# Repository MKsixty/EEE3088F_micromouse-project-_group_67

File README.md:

# EEE3088F_micromouse-project-_group_67

Overview

This repository contains the design files, documentation, and testing results for the sensor subsystem of a Micromouse robot, developed as part of the EEE3088F course at the University of Cape Town. The sensor board is designed as a custom PCB inspired by the UCLA Micromouse project but tailored through specific design decisions to meet project requirements and ensure optimal performance. Its primary role is to provide reliable wall detection on the front, left, and right sides of the Micromouse to enable autonomous maze navigation.

Design Summary

Emitters & Detectors: Uses IR333C infrared LEDs and TEFT4300 phototransistors, chosen for their closely matched wavelength (≈940 nm) for fast response and accurate detection.

Emitter Circuit: Powered by the 3.7 V LiPo battery, with 47 Ω current-limiting resistors ensuring ~70 mA drive for strong radiant intensity. 4.7 μF bypass capacitors filter noise on the LED supply.

Switching: Implemented with MMBF170 N-channel MOSFETs driven by STM32L476 PWM GPIOs. Gate resistors (100 Ω) and pulldowns (47 kΩ) ensure safe and stable operation.

Receiver Circuit: Uses a voltage divider (470 Ω & 1.5 kΩ) to keep outputs <3.3 V for STM32 ADC compatibility. A unity-gain buffer with LM324 op-amp protects ADC inputs from noise and spikes.

Form Factor: PCB dimensions ≤70 mm × 30 mm, cost-effective, and compatible with standard JLCPCB manufacturing limits.

Failure Management: Includes test points, through-hole components for easy rework, and jumper options to adjust resistor networks if needed.

Features

Accurate wall detection at up to 15 cm.

PWM-controlled IR switching for power efficiency.

Designed for direct integration with the STM32L476 processor board via a 14×2 pin header.

Supports three independent sensor channels (front, left, right).

Repository Contents

PCB design files and schematics.

Component datasheets (IR333C, TEFT4300, LM324, MOSFETs).

Integration code for STM32L476 (sensor readout and PWM control).

Project report, test logs, and acceptance test procedures.

Testing

The board underwent short-circuit checks, current consumption tests, PWM switching validation, and functional wall-detection tests. Issues such as LED orientation errors and interference between sensors were identified and mitigated using jumper reconfiguration and potential PWM timing adjustments in firmware.

Future Improvements

Implement time-multiplexed PWM driving to reduce crosstalk between sensors.

Optimize current draw to meet <100 mA power efficiency target.

Explore improved ADC filtering for cleaner sensor output.

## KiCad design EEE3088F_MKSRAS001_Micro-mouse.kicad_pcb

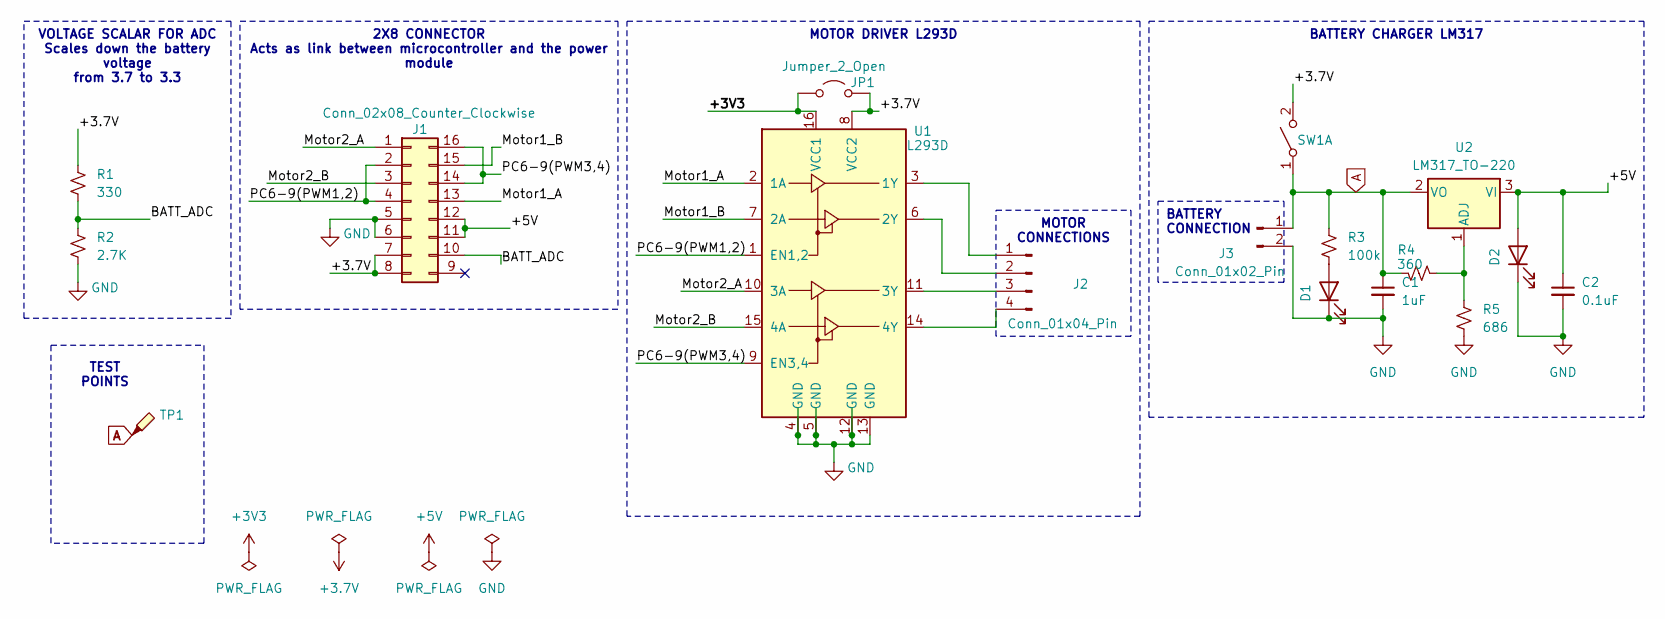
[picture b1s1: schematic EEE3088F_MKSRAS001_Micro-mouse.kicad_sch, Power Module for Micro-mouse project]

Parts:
C1: 1uF; C_0201_0603Metric
C2: 0.1uF; C_0201_0603Metric
D1, D2: LED; LED_0201_0603Metric
J1: Conn_02x08_Counter_Clockwise; JST_PUD_B16B-PUDSS_2x08_P2.00mm_Vertical
J2: Conn_01x04_Pin; PinHeader_1x04_P1.00mm_Vertical
J3: Conn_01x02_Pin; JST_PH_B2B-PH-K_1x02_P2.00mm_Vertical
JP1: Jumper_2_Open; KEYSTONE_5110
R1: 330; R_0201_0603Metric
R2: 2.7K; R_0201_0603Metric
R3: 100k; R_0201_0603Metric
R4: 360; R_0201_0603Metric
R5: 686; R_0201_0603Metric
SW1: SW_DPST_x2; SW_DIP_SPSTx01_Slide_Omron_A6S-110x_W8.9mm_P2.54mm
TP1: TestPoint_Probe; Pin_D1.0mm_L10.0mm
U1: L293D; DIP-16_W7.62mm
U2: LM317_TO-220; TO-220-3_Vertical

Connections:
+3.7V: J1.7, J1.8, JP1.2 (B), R1.1, SW1.2 (B), U1.8 (VCC2)
+3V3: JP1.1 (A), U1.16 (VCC1)
+5V: C2.1, D2.2 (A), J1.11, J1.12, U2.3 (VI)
/BATT_ADC: J1.10, R1.2, R2.1
/Motor1_A: J1.13, U1.2 (1A)
/Motor1_B: J1.15, U1.7 (2A)
/Motor2_A: J1.1, U1.10 (3A)
/Motor2_B: J1.3, U1.15 (4A)
/PC6-9(PWM1,2): J1.2, J1.4, U1.1 (EN1,2)
/PC6-9(PWM3,4): J1.14, J1.16, U1.9 (EN3,4)
A: C1.1, J3.1, R3.1, R4.2, SW1.1 (A), TP1.1, U2.2 (VO)
GND: C1.2, C2.2, D1.1 (K), D2.1 (K), J1.5, J1.6, J3.2, R2.2, R5.2, U1.4 (GND), U1.5 (GND), U1.12 (GND), U1.13 (GND)
unnamed: D1.2 (A), R3.2
unnamed: J2.1, U1.3 (1Y)
unnamed: J2.2, U1.6 (2Y)
unnamed: J2.3, U1.11 (3Y)
unnamed: J2.4, U1.14 (4Y)
unnamed: R4.1, R5.1, U2.1 (ADJ)

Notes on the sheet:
2X8 CONNECTOR Acts as link between microcontroller and the power module
BATTERY CHARGER LM317
MOTOR DRIVER L293D
BATTERY CONNECTION
TEST POINTS
MOTOR CONNECTIONS
VOLTAGE SCALAR FOR ADC Scales down the battery voltage from 3.7 to 3.3

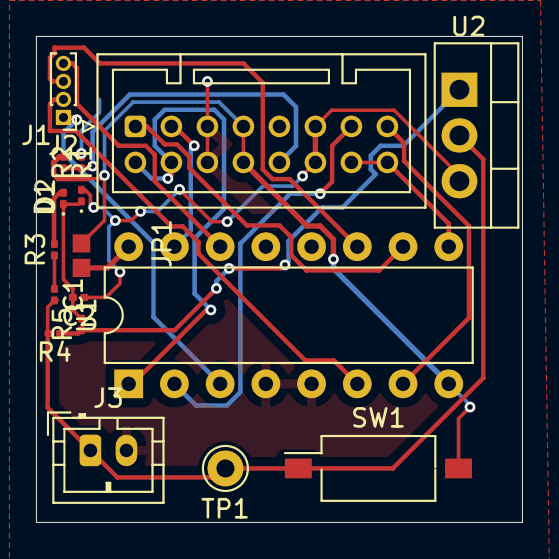
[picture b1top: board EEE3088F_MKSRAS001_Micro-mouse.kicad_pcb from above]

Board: 2 copper layers, 27.0 x 27.0 mm, 17 parts (0 on the bottom side), 18 nets.

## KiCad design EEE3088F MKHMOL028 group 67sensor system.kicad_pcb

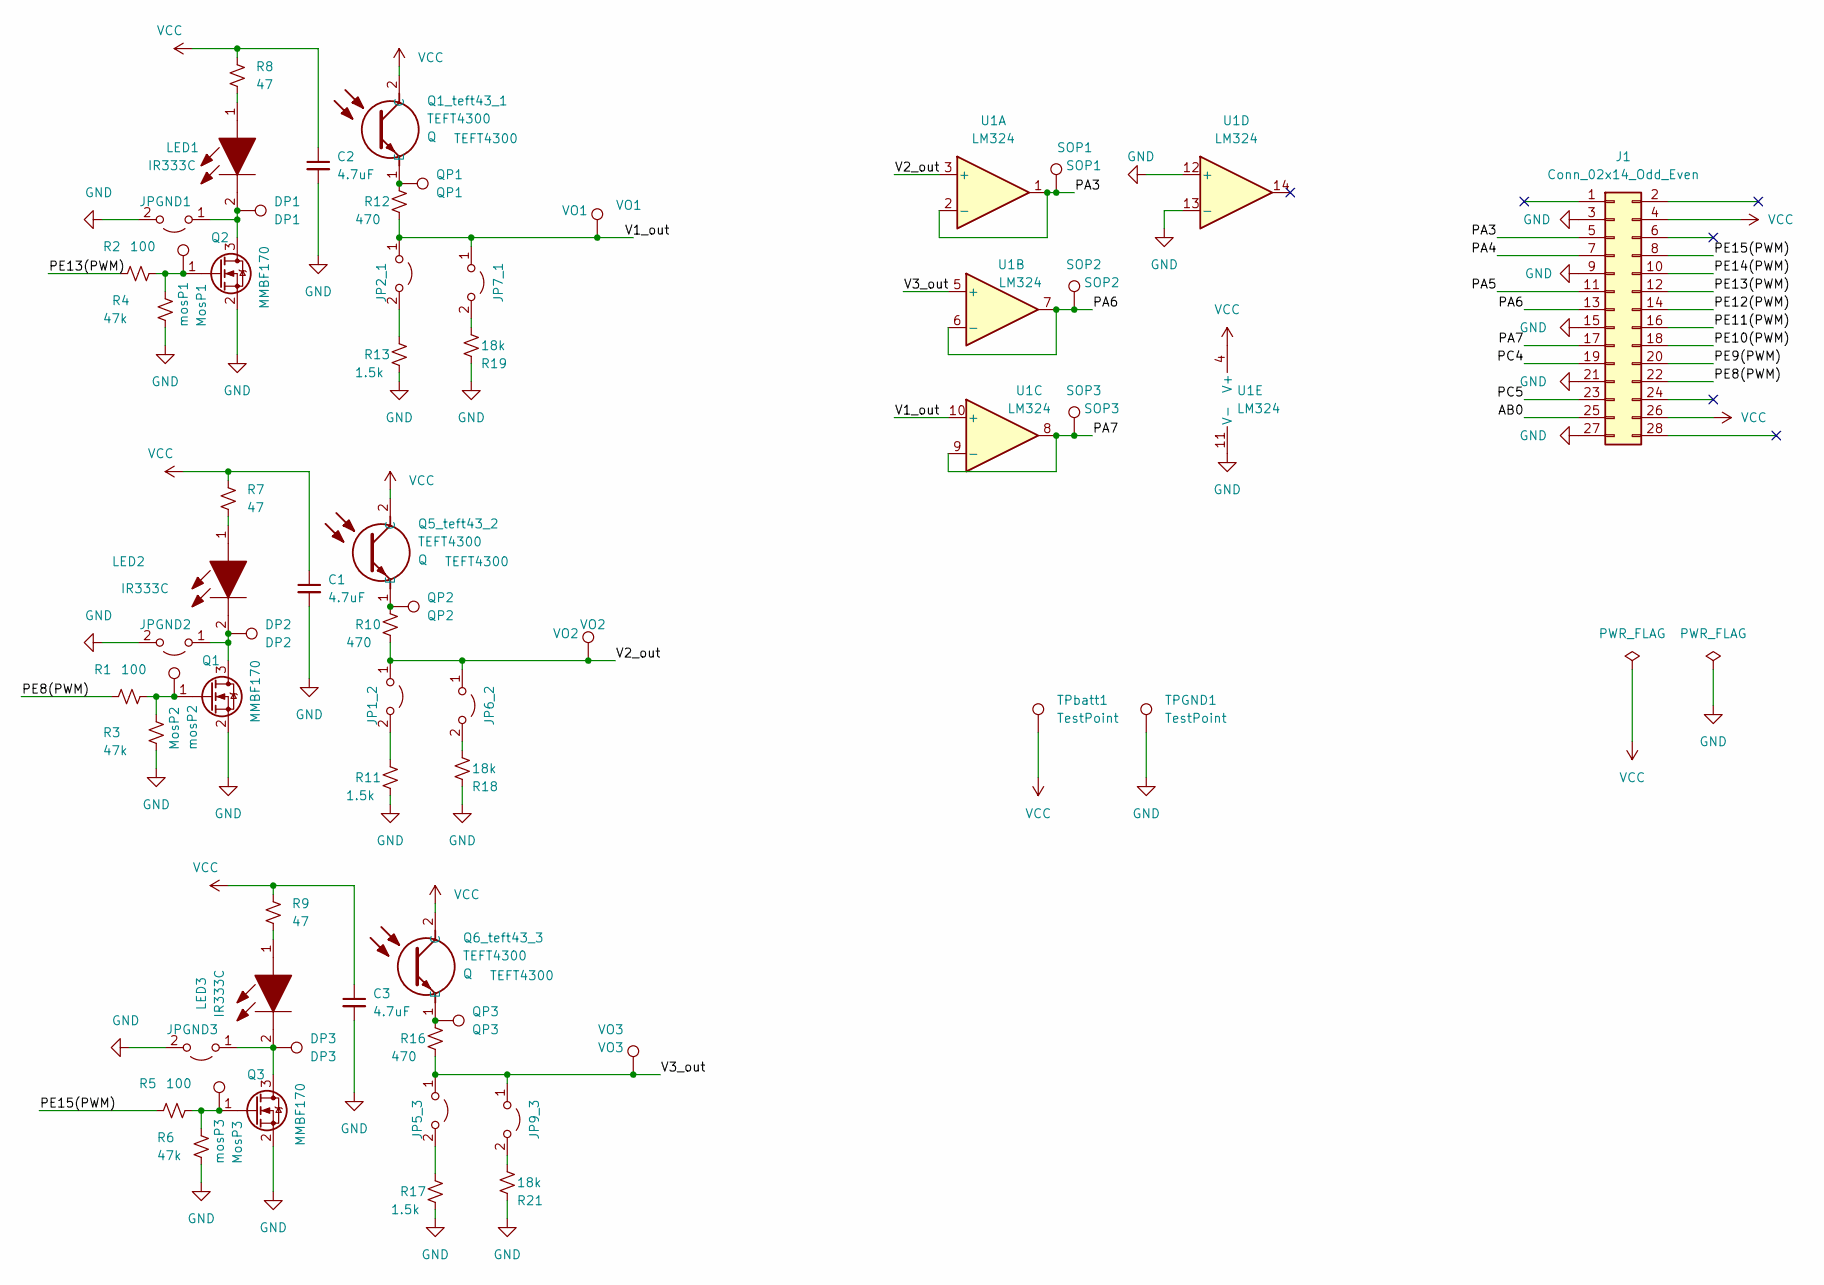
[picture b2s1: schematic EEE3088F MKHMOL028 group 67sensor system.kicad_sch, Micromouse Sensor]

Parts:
C1, C2, C3: 4.7uF; C_0805_2012Metric
DP1: DP1; TestPoint_Pad_1.0x1.0mm
DP2: DP2; TestPoint_Pad_1.0x1.0mm
DP3: DP3; TestPoint_Pad_1.0x1.0mm
J1: Conn_02x14_Odd_Even; PinHeader_2x14_P2.54mm_Vertical
JP1_2, JP2_1, JP5_3, JP6_2, JP7_1, JP9_3: Jumper_2_Open; SolderJumper-2_P1.3mm_Open_RoundedPad1.0x1.5mm
JPGND1, JPGND2, JPGND3: Jumper_2_Open; SolderJumper-2_P1.3mm_Open_RoundedPad1.0x1.5mm
LED1, LED2, LED3: IR333C; LED_D3.0mm_Horizontal_O1.27mm_Z2.0mm_Clear; Mouser Part Number 638-IR333C
Q1, Q2, Q3: MMBF170; SOT-23
Q1_teft43_1, Q5_teft43_2, Q6_teft43_3: TEFT4300; LED_D3.0mm_Horizontal_O1.27mm_Z2.0mm_IRBlack; Mouser Part Number 782-TEFT4300
QP1: QP1; TestPoint_Pad_1.0x1.0mm
QP2: QP2; TestPoint_Pad_1.0x1.0mm
QP3: QP3; TestPoint_Pad_D1.0mm
R1, R2, R5: 100; R_0805_2012Metric_Pad1.20x1.40mm_HandSolder
R3, R4, R6: 47k; R_0805_2012Metric
R7, R8, R9: 47; R_0805_2012Metric_Pad1.20x1.40mm_HandSolder
R10, R12, R16: 470; R_0805_2012Metric_Pad1.20x1.40mm_HandSolder
R11, R13, R17: 1.5k; R_0805_2012Metric_Pad1.20x1.40mm_HandSolder
R18, R19, R21: 18k; R_0805_2012Metric_Pad1.20x1.40mm_HandSolder
SOP1: SOP1; TestPoint_Pad_1.0x1.0mm
SOP2: SOP2; TestPoint_Pad_1.0x1.0mm
SOP3: SOP3; TestPoint_Pad_1.0x1.0mm
TPGND1: TestPoint; TestPoint_Pad_1.0x1.0mm
TPbatt1: TestPoint; TestPoint_Pad_D1.0mm
U1: LM324; SOIC-14_3.9x8.7mm_P1.27mm
VO1: VO1; TestPoint_Pad_D1.5mm
VO2: VO2; TestPoint_Pad_D1.0mm
VO3: VO3; TestPoint_Pad_D1.5mm
mosP1: MosP1; TestPoint_Pad_1.0x1.0mm
mosP2: MosP2; TestPoint_Pad_1.0x1.0mm
mosP3: MosP3; TestPoint_Pad_1.0x1.0mm

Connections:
/AB0: J1.25
/PA3: J1.5, SOP1.1, U1.1, U1.2 (-)
/PA4: J1.7
/PA5: J1.11
/PA6: J1.13, SOP2.1, U1.6 (-), U1.7
/PA7: J1.17, SOP3.1, U1.8, U1.9 (-)
/PC4: J1.19
/PC5: J1.23
/PE8(PWM): J1.22, R1.2
/PE9(PWM): J1.20
/PE10(PWM): J1.18
/PE11(PWM): J1.16
/PE12(PWM): J1.14
/PE13(PWM): J1.12, R2.2
/PE14(PWM): J1.10
/PE15(PWM): J1.8, R5.2
/V1_out: JP2_1.1 (A), JP7_1.1 (A), R12.1, U1.10 (+), VO1.1
/V2_out: JP1_2.1 (A), JP6_2.1 (A), R10.1, U1.3 (+), VO2.1
/V3_out: JP5_3.1 (A), JP9_3.1 (A), R16.1, U1.5 (+), VO3.1
GND: C1.2, C2.2, C3.2, J1.3, J1.9, J1.15, J1.21, J1.27, JPGND1.2 (B), JPGND2.2 (B), JPGND3.2 (B), Q1.2 (S), Q2.2 (S), Q3.2 (S), R3.1, R4.1, R6.1, R11.1, R13.1, R17.1, R18.1, R19.1, R21.1, TPGND1.1, U1.11 (V-), U1.12 (+), U1.13 (-)
unnamed: DP2.1, JPGND2.1 (A), LED2.2, Q1.3 (D)
unnamed: DP3.1, JPGND3.1 (A), LED3.2, Q3.3 (D)
unnamed: JP1_2.2 (B), R11.2
unnamed: JP2_1.2 (B), R13.2
unnamed: JP5_3.2 (B), R17.2
unnamed: JP6_2.2 (B), R18.2
unnamed: JP7_1.2 (B), R19.2
unnamed: JP9_3.2 (B), R21.2
unnamed: LED1.1, R8.1
unnamed: DP1.1, JPGND1.1 (A), LED1.2, Q2.3 (D)
unnamed: LED2.1, R7.1
unnamed: LED3.1, R9.1
unnamed: Q1_teft43_1.1 (E), QP1.1, R12.2
unnamed: Q5_teft43_2.1 (E), QP2.1, R10.2
unnamed: Q6_teft43_3.1 (E), QP3.1, R16.2
unnamed: Q1.1 (G), R1.1, R3.2, mosP2.1
unnamed: Q2.1 (G), R2.1, R4.2, mosP1.1
unnamed: Q3.1 (G), R5.1, R6.2, mosP3.1
VCC: C1.1, C2.1, C3.1, J1.4, J1.26, Q1_teft43_1.2 (C), Q5_teft43_2.2 (C), Q6_teft43_3.2 (C), R7.2, R8.2, R9.2, TPbatt1.1, U1.4 (V+)

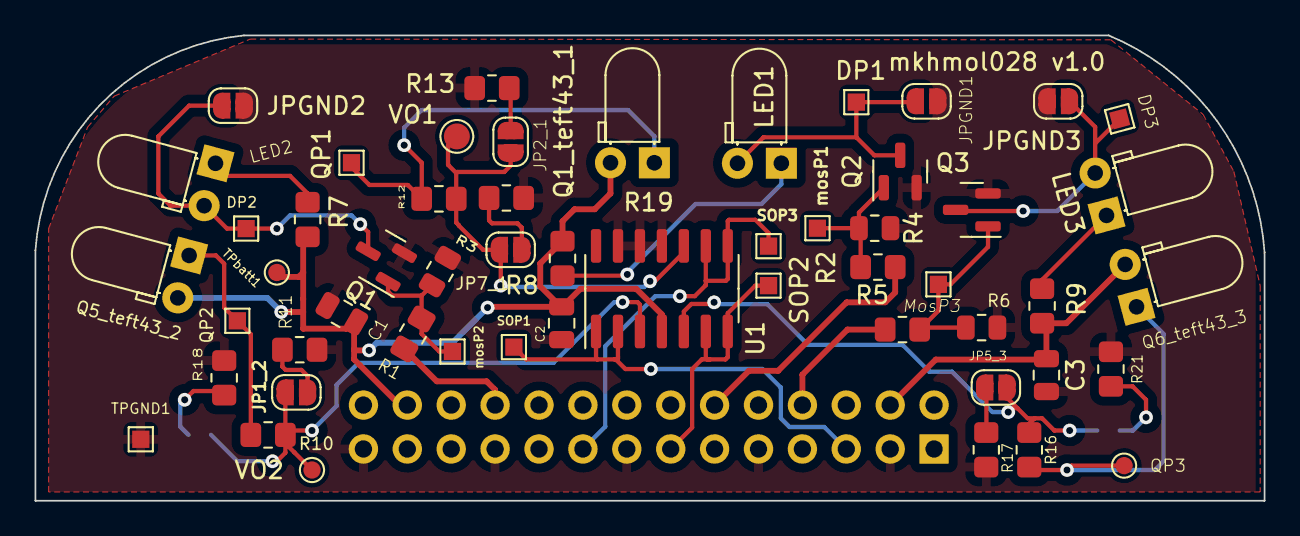
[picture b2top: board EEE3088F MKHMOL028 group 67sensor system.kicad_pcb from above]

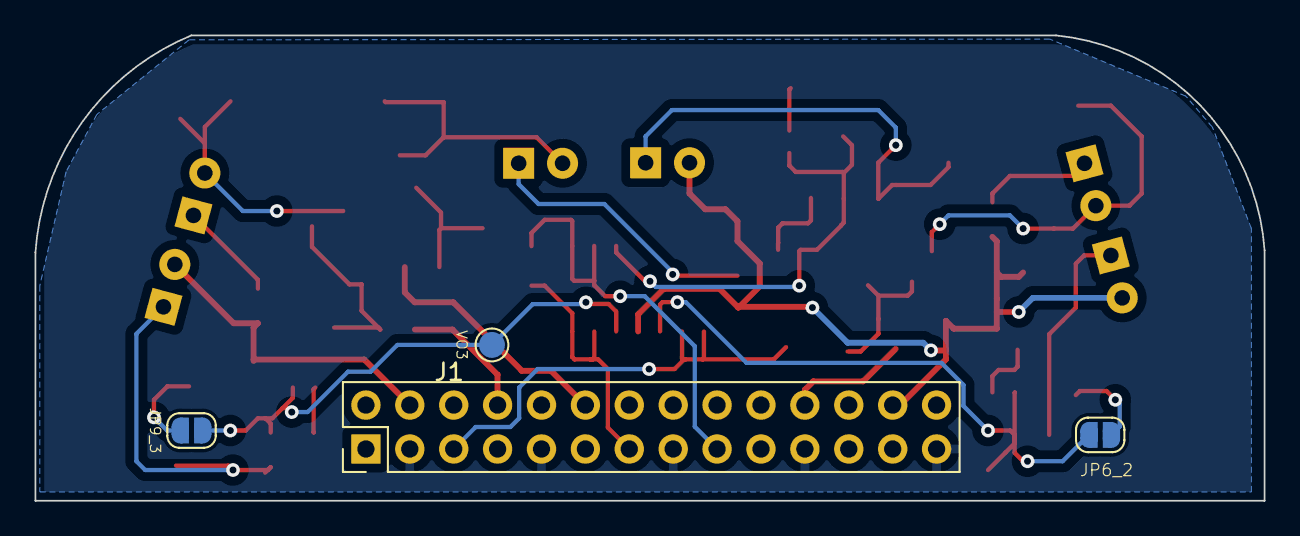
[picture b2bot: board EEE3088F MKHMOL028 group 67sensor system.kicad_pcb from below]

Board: 2 copper layers, 71.1 x 26.9 mm, 58 parts (4 on the bottom side), 29 nets.

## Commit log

2024-04-20 Add files via upload
    first commit of the PCB design
2024-04-21 Datasheets_for_Power_module
2024-04-21 Add files via upload
    datasheet commitment
2025-08-21 Molise _sensor board documentation
